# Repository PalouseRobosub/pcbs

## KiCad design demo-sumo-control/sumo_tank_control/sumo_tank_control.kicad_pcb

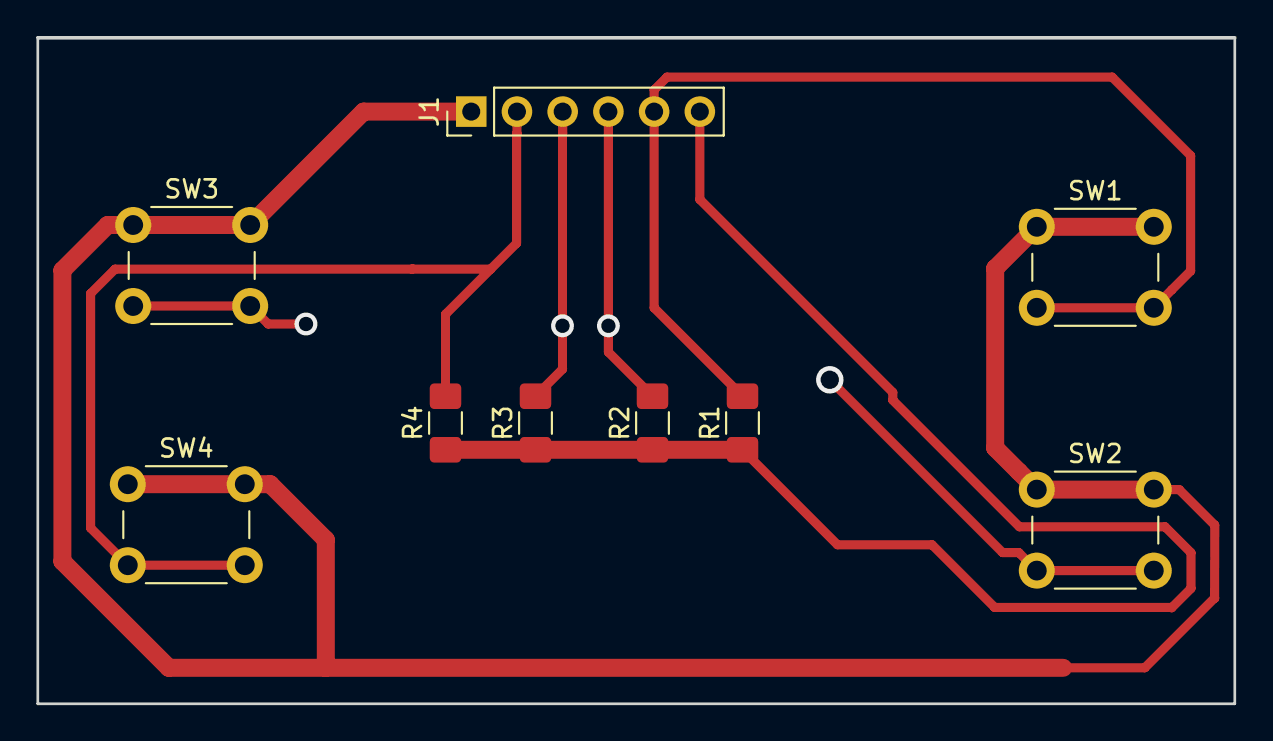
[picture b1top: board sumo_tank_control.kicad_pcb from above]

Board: 2 copper layers, 66.5 x 37.0 mm, 9 parts (0 on the bottom side), 6 nets.

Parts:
J1: Conn_01x06; PinHeader_1x06_P2.54mm_Vertical
R1, R2, R3, R4: 6k; R_1206_3216Metric_Pad1.42x1.75mm_HandSolder
SW1, SW2, SW3, SW4: SW_Push; SW_PUSH_6mm_H5mm

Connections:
+3V3: J1.6, R1.1, R2.1, R3.1, R4.1
/GPIO_0: J1.5, R1.2, SW1.2
/GPIO_1: J1.4, R2.2, SW2.2
/GPIO_2: J1.3, R3.2, SW3.2
/GPIO_3: J1.2, R4.2, SW4.2
GND: J1.1, SW1.1, SW2.1, SW3.1, SW4.1

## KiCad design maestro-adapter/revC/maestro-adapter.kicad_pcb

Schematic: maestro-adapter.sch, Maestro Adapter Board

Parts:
P1: CONN_01X07; Pin_Header_Straight_1x07; part number S7040-ND
P2, P3, P4, P5, P6, P7, P8, P9, P10, P11, P12, P13, P16: CONN_01X03; Pin_Header_Straight_1x03; part number S7036-ND
P14, P15: CONN_01X06; JST_PUD; part number 455-2485-ND
R1, R2, R3, R4, R5, R6, R7, R8, R9, R10, R11, R12, R13, R14, R15, R16: 0; R_0603_HandSoldering; part number 311-0.0GRCT-ND
U1, U2: Si866x; SOIC-16_3.9x9.9mm_Pitch1.27mm; part number 336-2115-5-ND
W1, W2, W3, W4, W5, W6, W7, W8, W9, W10, W11, W12: TEST_1P; Measurement_Point_Round-TH_Small

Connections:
+5V: P1.2, P2.2, P3.2, P4.2, P5.2, P6.2, P7.2, P8.2, P9.2, P10.2, P11.2, P12.2, P13.2, P16.1, P16.2, U1.1 (Vdd_1), U2.1 (Vdd_1)
/bec_esc_1: P14.3, U1.16 (Vdd_2), W9.1
/bec_esc_2: P15.3, U2.16 (Vdd_2), W10.1
/bec_gnd_1: P14.1, U1.9 (Gnd_2), W11.1
/bec_gnd_2: P15.1, U2.9 (Gnd_2), W12.1
/sig1: P8.1, R1.2
/sig1_in: R1.1, R9.2, U1.5 (A4)
/sig1_isolated: P14.4, U1.12 (B4), W1.1
/sig2: P7.1, R2.2
/sig2_in: R2.1, R10.2, U1.4 (A3)
/sig2_isolated: P14.2, U1.13 (B3), W2.1
/sig3: P10.1, R3.2
/sig3_in: R3.1, R11.2, U1.3 (A2)
/sig3_isolated: P14.6, U1.14 (B2), W3.1
/sig4: P11.1, R4.2
/sig4_in: R4.1, R12.2, U1.2 (A1)
/sig4_isolated: P14.5, U1.15 (B1), W4.1
/sig5: P12.1, R5.2
/sig5_in: R5.1, R13.1, U2.2 (A1)
/sig5_isolated: P15.5, U2.15 (B1), W5.1
/sig6: P13.1, R6.2
/sig6_in: R6.1, R14.1, U2.3 (A2)
/sig6_isolated: P15.2, U2.14 (B2), W6.1
/sig7: P5.1, R7.2
/sig7_in: R7.1, R15.1, U2.4 (A3)
/sig7_isolated: P15.6, U2.13 (B3), W7.1
/sig8: P6.1, R8.2
/sig8_in: R8.1, R16.1, U2.5 (A4)
/sig8_isolated: P15.4, U2.12 (B4), W8.1
/t1: P2.1, R9.1, R13.2
/t2: P3.1, R10.1, R14.2
/t3: P4.1, R11.1, R15.2
/t4: P9.1, R12.1, R16.2
GND: P1.1, P2.3, P3.3, P4.3, P5.3, P6.3, P7.3, P8.3, P9.3, P10.3, P11.3, P12.3, P13.3, P16.3, U1.8 (Gnd_1), U2.8 (Gnd_1)

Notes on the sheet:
Signal Isolators
Thruster Signals 1-4
Thruster Signals 5-8
Thruster Signals 9-12
Maestro Power Header
Thruster Case Cable Bundles
Case #2
Solder bridges can be used to short over different signals to different inputs on the isolators. This is for potential faults within the maestro.
Solder bridge connections must be shorted to mux inputs for the input signals to be transmitted.
Test Points
Power Connector
Maestro Connections
Note: tx signals are unused maestro PWM connections.
Solder Bridges
Case #1
This section intentionally left blank.

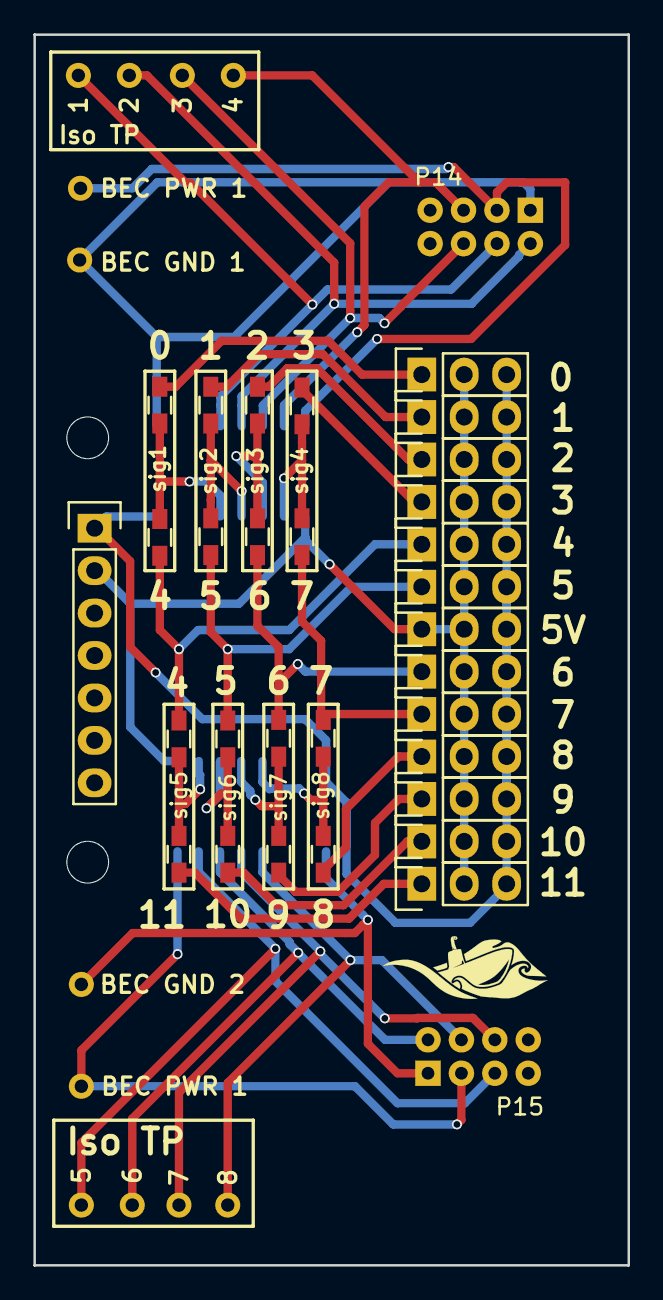
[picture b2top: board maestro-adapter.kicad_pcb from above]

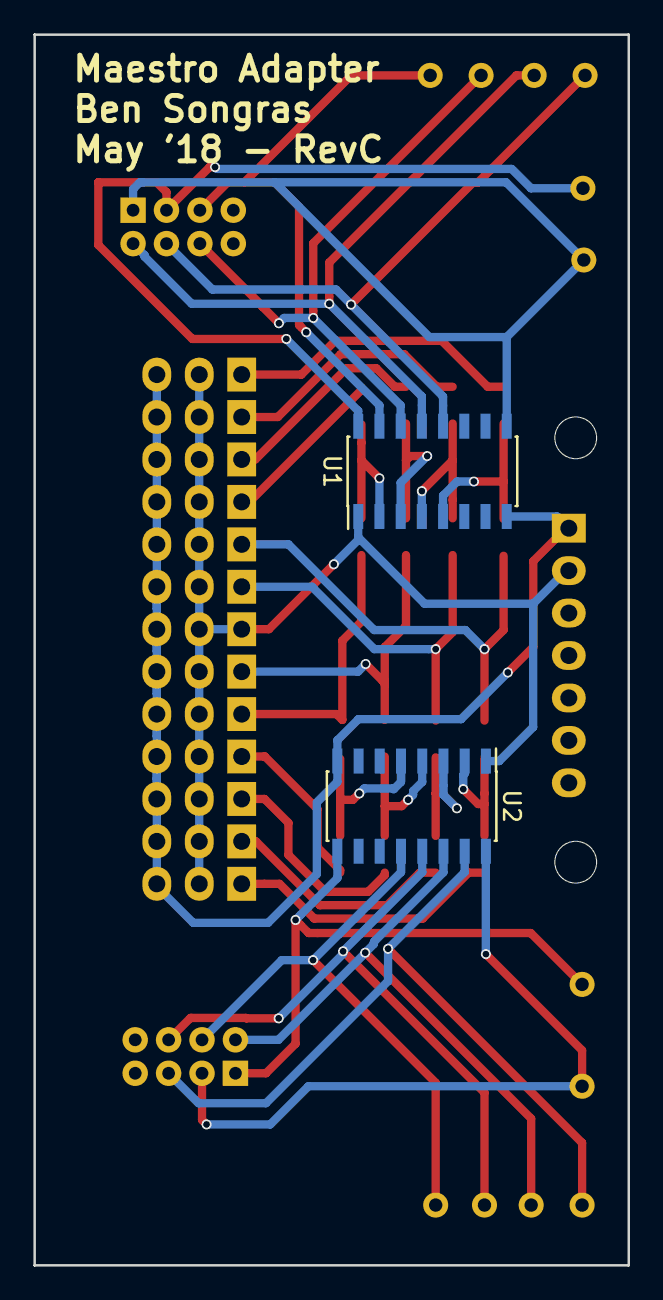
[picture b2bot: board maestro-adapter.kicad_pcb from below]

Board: 2 copper layers, 35.6 x 73.7 mm, 46 parts (2 on the bottom side), 34 nets.

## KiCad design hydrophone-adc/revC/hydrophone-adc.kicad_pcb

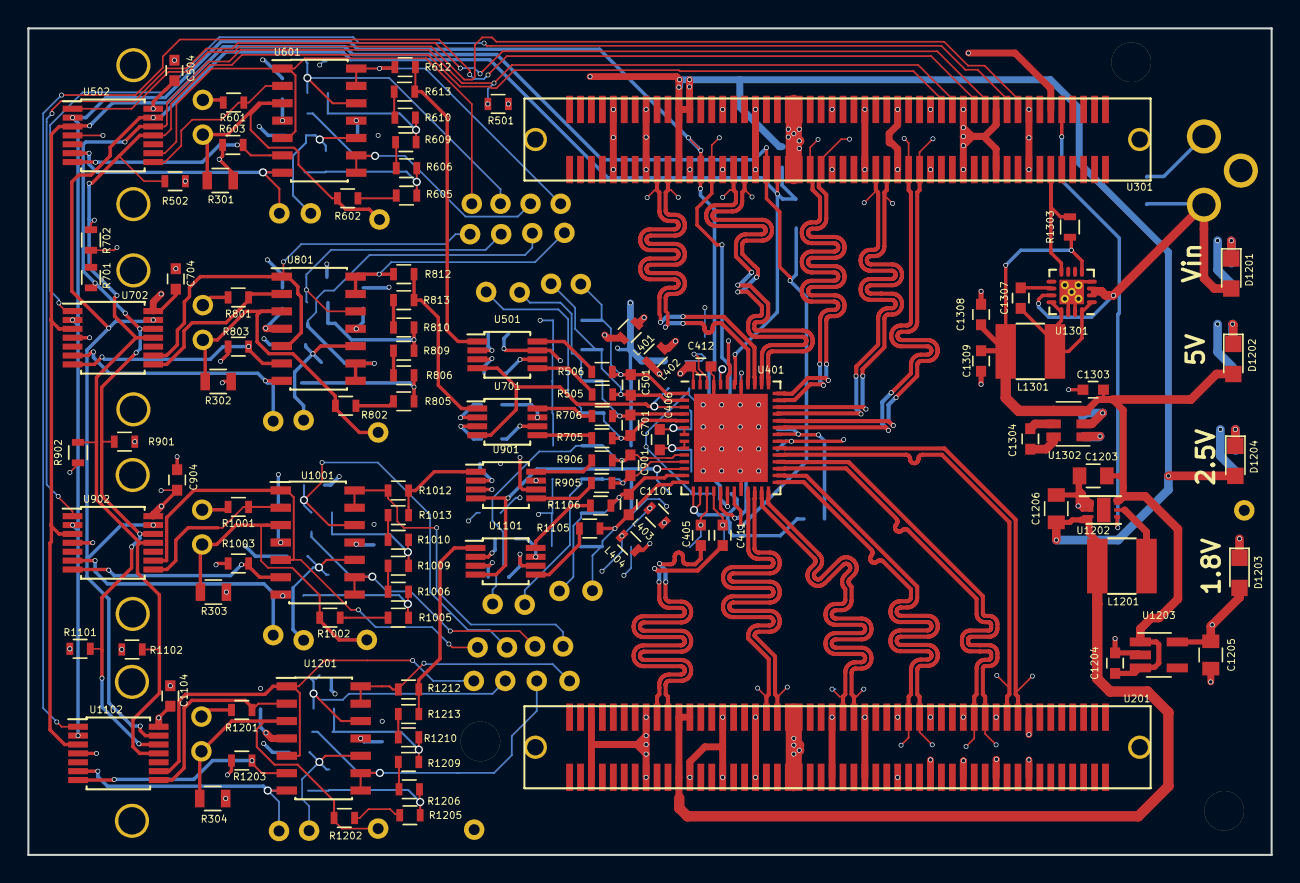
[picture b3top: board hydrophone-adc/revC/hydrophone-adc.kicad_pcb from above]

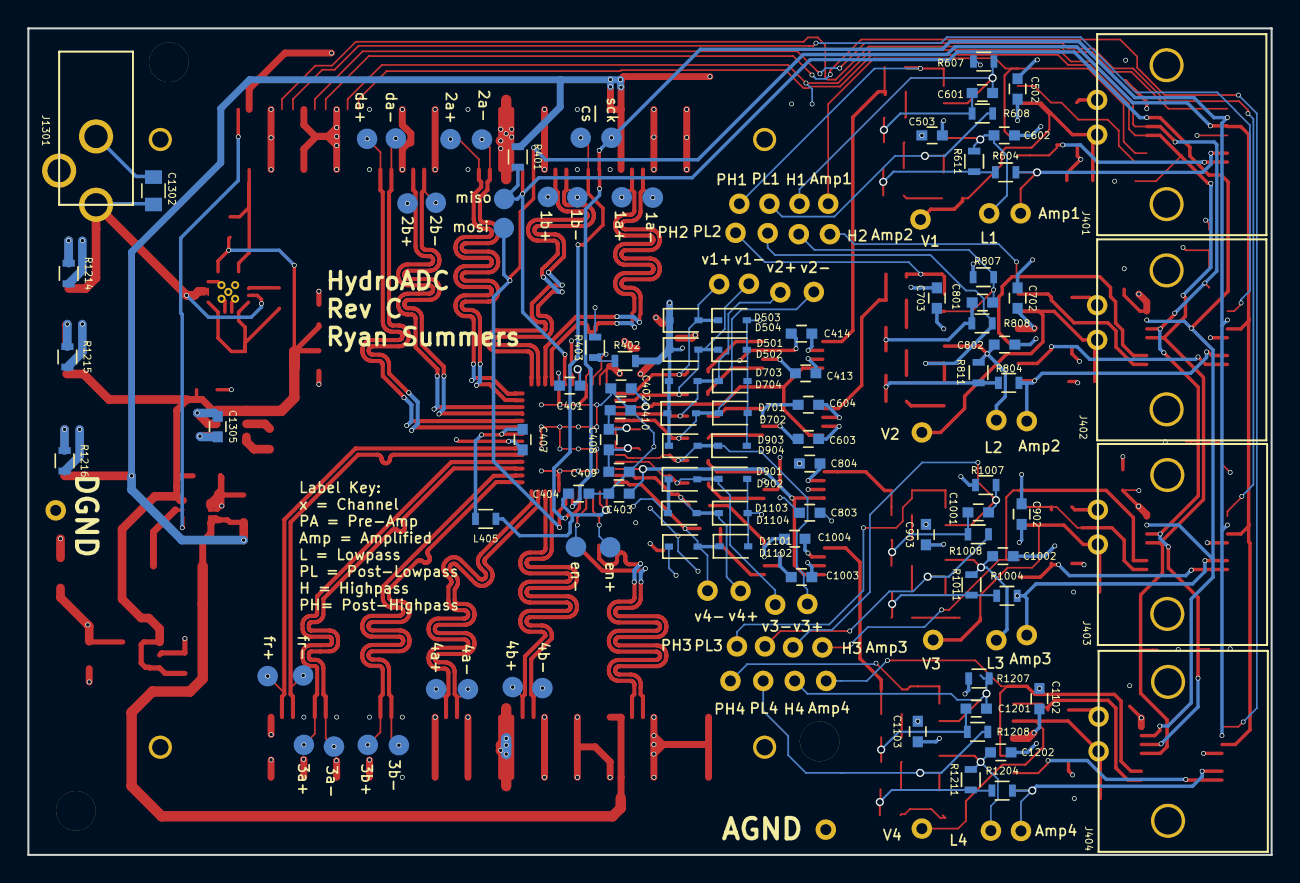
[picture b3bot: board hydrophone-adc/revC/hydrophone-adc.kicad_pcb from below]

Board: 4 copper layers, 90.9 x 60.5 mm, 249 parts (104 on the bottom side), 134 nets.

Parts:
C401, C412, C1204, C1304: 1u; C_0603
C402, C403, C404, C405, C406, C407, C409, C410, C411, C413, C414, C502, C503, C504, C603, C604, C702, C703, C704, C803, C804, C902, C903, C904, C1003, C1004, C1102, C1103, C1104: 100n; C_0603
C408, C1303, C1305: 2.2u; C_0603
C501, C701, C901, C1101: 10n; C_0603
C601, C602, C801, C802, C1001, C1002, C1201, C1202: 1n; C_0603
C1203, C1205, C1206, C1302: 10u; C_0805
C1307: 22n; C_0603
C1308, C1309: 22u; C_0603
D501, D502, D503, D504, D701, D702, D703, D704, D901, D902, D903, D904, D1101, D1102, D1103, D1104: D_Schottky; D_SOD-323
D1201: YLW; LED_0805
D1202: RED; LED_0805
D1203, D1204: GRN; LED_0805
J401, J402, J403, J404: CONN_COAXIAL; BNC-Coax-TE
J501, J502, J601, J602, J603, J604, J605, J606, J607, J701, J702, J801, J802, J803, J804, J805, J806, J807, J901, J902, J1001, J1002, J1003, J1004, J1005, J1006, J1007, J1101, J1102, J1201, J1202, J1203, J1204, J1205, J1206, J1207: TEST_1P; Measurement_Point_Round-TH_Small
J1301: BARREL_JACK; BarrelJack-CUI
L401, L402, L403, L404, L405: Ferrite_Bead; R_0603
L1201, L1301: 4.7u; Inductor-3.6mm-Pitch-4.0mm-Length-1.5mm-Width
R301, R302, R303, R304: 100k; R_0805
R401: 2k; R_0603
R402, R403, R602, R604, R605, R606, R608, R609, R610, R612, R613, R802, R804, R805, R806, R808, R809, R810, R812, R813, R1002, R1004, R1005, R1006, R1008, R1009, R1010, R1012, R1013, R1202, R1204, R1205, R1206, R1208, R1209, R1210, R1212, R1213: 0; R_0603
R501, R502, R601, R603, R607, R701, R702, R801, R803, R807, R901, R902, R1001, R1003, R1007, R1101, R1102, R1201, R1203, R1207, R1303: 10k; R_0603
R505, R506, R705, R706, R905, R906, R1105, R1106: 100; R_0603
R611, R811, R1011, R1211: 3.16k; R_0603
R1214, R1215: 1k; R_0603
R1216: 500; R_0603
TP301, TP302, TP303, TP304, TP305, TP306, TP307, TP308, TP309, TP310, TP311, TP312, TP313, TP314, TP315, TP316, TP317, TP318, TP319, TP320, TP321, TP322, TP323, TP324, TP325, TP326: TEST; Measurement_Point_Round-SMD-Pad_Small
TP327, TP328: TEST; Measurement_Point_Round-TH_Small
U201: micro-zed-jx1; fci-61083-2x50
U301: micro-zed-jx2; fci-61083-2x50
U401: LTC2171-14; QFN-52-1EP_7x8mm_Pitch0.5mm
U501, U701, U901, U1101: el5170; MSOP-8_3x3mm_Pitch0.65mm
U502, U702, U902, U1102: MCP42x1; TSSOP-14_4.4x5mm_Pitch0.65mm
U601, U801, U1001, U1201: LM324; SOIC-14_3.9x8.7mm_Pitch1.27mm
U1202: XC9261; UFDFN-6
U1203: xc6222; SOT-23-5_HandSoldering
U1301: TS30013; QFN-16-1EP_3x3mm_Pitch0.5mm_ThermalVias
U1302: LM2776; SOT-23-6

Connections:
+1V8: C407.1, C1205.1, D501.1, D503.1, D701.1, D703.1, D901.1, D903.1, D1101.1, D1103.1, D1203.2, L405.2, R402.2, U401.34, U1203.5
+2V5: C504.1, C704.1, C904.1, C1104.1, C1206.1, D1204.2, L1201.2, R401.1, R501.1, R502.1, R701.1, R702.1, R901.1, R902.1, R1101.1, R1102.1, U201.78, U201.79, U201.80, U301.78, U301.79, U301.80, U502.14, U702.14, U902.14, U1102.14, U1202.3
+5V: C413.1, C502.1, C603.1, C702.1, C803.1, C902.1, C1003.1, C1102.1, C1203.1, C1204.1, C1303.1, C1308.1, C1309.1, D1202.2, L1301.2, R1303.1, U201.57, U201.58, U201.59, U201.60, U301.12, U301.57, U301.58, U301.59, U301.60, U501.6, U601.4, U701.6, U801.4, U901.6, U1001.4, U1101.6, U1201.4, U1202.6, U1203.1, U1203.3, U1301.5, U1302.3, U1302.4
-5V: C414.1, C503.1, C604.1, C703.1, C804.1, C903.1, C1004.1, C1103.1, C1305.1, U501.7, U601.11, U701.7, U801.11, U901.7, U1001.11, U1101.7, U1201.11, U1302.1
/ADC/1v8_analog: C404.1, C412.1, L405.1, U401.15, U401.16, U401.51, U401.52
/ADC/Diff Conv1/Vin: R612.1, R613.1, U501.1
/ADC/Diff Conv1/v+: R506.1, U501.8
/ADC/Diff Conv1/v-: R505.1, U501.5
/ADC/Diff Conv2/Vin: R812.1, R813.1, U701.1
/ADC/Diff Conv2/v+: R706.1, U701.8
/ADC/Diff Conv2/v-: R705.1, U701.5
/ADC/Diff Conv3/Vin: R1012.1, R1013.1, U901.1
/ADC/Diff Conv3/v+: R906.1, U901.8
/ADC/Diff Conv3/v-: R905.1, U901.5
/ADC/Diff Conv4/Vin: R1212.1, R1213.1, U1101.1
/ADC/Diff Conv4/v+: R1106.1, U1101.8
/ADC/Diff Conv4/v-: R1105.1, U1101.5
/ADC/Filter1/P0A: R601.2, U502.8, U601.2
/ADC/Filter1/P0W: J602.1, U502.9, U601.1, U601.5
/ADC/Filter1/P1A: R603.2, U502.7, U601.6
/ADC/Filter1/P1W: J603.1, R604.2, U502.6, U601.7
/ADC/Filter1/Vin: J401.1, J601.1, R301.1, R602.1, U601.3
/ADC/Filter2/P0A: R801.2, U702.8, U801.2
/ADC/Filter2/P0W: J802.1, U702.9, U801.1, U801.5
/ADC/Filter2/P1A: R803.2, U702.7, U801.6
/ADC/Filter2/P1W: J803.1, R804.2, U702.6, U801.7
/ADC/Filter2/Vin: J402.1, J801.1, R302.1, R802.1, U801.3
/ADC/Filter3/P0A: R1001.2, U902.8, U1001.2
/ADC/Filter3/P0W: J1002.1, U902.9, U1001.1, U1001.5
/ADC/Filter3/P1A: R1003.2, U902.7, U1001.6
/ADC/Filter3/P1W: J1003.1, R1004.2, U902.6, U1001.7
/ADC/Filter3/Vin: J403.1, J1001.1, R303.1, R1002.1, U1001.3
/ADC/Filter4/P0A: R1201.2, U1102.8, U1201.2
/ADC/Filter4/P0W: J1202.1, U1102.9, U1201.1, U1201.5
/ADC/Filter4/P1A: R1203.2, U1102.7, U1201.6
/ADC/Filter4/P1W: J1203.1, R1204.2, U1102.6, U1201.7
/ADC/Filter4/Vin: J404.1, J1201.1, R304.1, R1202.1, U1201.3
/ADC/Vcm12: C402.1, U401.3, U501.4, U701.4
/ADC/Vcm34: C403.1, U401.12, U901.4, U1101.4
/ADC/enc+: C405.2, TP317.1, U401.17
/ADC/enc-: C411.2, TP318.1, U401.18
/ADC/v1+: C501.2, D503.2, D504.1, J502.1, R506.2, U401.1
/ADC/v1-: C501.1, D501.2, D502.1, J501.1, R505.2, U401.2
/ADC/v2+: C701.2, D703.2, D704.1, J702.1, R706.2, U401.4
/ADC/v2-: C701.1, D701.2, D702.1, J701.1, R705.2, U401.5
/ADC/v3+: C901.2, D903.2, D904.1, J902.1, R906.2, U401.10
/ADC/v3-: C901.1, D901.2, D902.1, J901.1, R905.2, U401.11
/ADC/v4+: C1101.2, D1103.2, D1104.1, J1102.1, R1106.2, U401.13
/ADC/v4-: C1101.1, D1101.2, D1102.1, J1101.1, R1105.2, U401.14
/MISO: R401.2, TP321.1, U301.61, U401.46, U502.13, U702.13, U902.13, U1102.13
/MOSI: TP322.1, U301.63, U401.21, U502.3, U702.3, U902.3, U1102.3
/MicroZed-JX2/LVDS1+: U301.18, U502.1
/MicroZed-JX2/LVDS1-: U301.20, U702.1
/MicroZed-JX2/LVDS3+: U301.24, U902.1
/MicroZed-JX2/LVDS3-: U301.26, U1102.1
/MicroZed-JX2/LVDS5+: R501.2, R701.2, R901.2, R1101.2, U301.30, U502.12, U702.12, U902.12, U1102.12
/MicroZed-JX2/LVDS5-: R502.2, R702.2, R902.2, R1102.2, U301.32, U502.11, U702.11, U902.11, U1102.11
/Power/Vin: C1302.1, D1201.2, J1301.1, U1301.2, U1301.3, U1301.11
/SCK: TP319.1, U301.75, U401.20, U502.2, U702.2, U902.2, U1102.2
/data_clk+: TP325.1, U301.35, U401.36
/data_clk-: TP326.1, U301.37, U401.35
/enc+: C405.1, U201.82
/enc-: C411.1, U201.84
/fr_clk+: TP323.1, U201.18, U401.32
/fr_clk-: TP324.1, U201.20, U401.31
/out1a+: TP301.1, U301.81, U401.44
/out1a-: TP309.1, U301.83, U401.43
/out1b+: TP310.1, U301.67, U401.42
/out1b-: TP302.1, U301.69, U401.41
/out2a+: TP303.1, U301.53, U401.40
/out2a-: TP311.1, U301.55, U401.39
/out2b+: TP312.1, U301.41, U401.38
/out2b-: TP304.1, U301.43, U401.37
/out3a+: TP305.1, U201.24, U401.30
/out3a-: TP313.1, U201.26, U401.29
/out3b+: TP314.1, U201.36, U401.28
/out3b-: TP306.1, U201.38, U401.27
/out4a+: TP315.1, U201.48, U401.26
/out4a-: TP307.1, U201.50, U401.25
/out4b+: TP316.1, U201.62, U401.24
/out4b-: TP308.1, U201.64, U401.23
/v_good: R1303.2, U301.11, U1301.8
/vccio_en: U301.10, U1202.4
/~CS: TP320.1, U301.73, U401.19
GND: C407.2, C1203.2, C1204.2, C1205.2, C1206.2, C1302.2, C1303.2, C1305.2, C1308.2, C1309.2, D1203.1, J1301.2, L401.1, L402.1, L403.1, L404.1, R403.1, R1214.2, R1215.2, R1216.2, TP327.1, U201.15, U201.16, U201.21, U201.22, U201.27, U201.28, U201.33, U201.34, U201.39, U201.40, U201.45, U201.46, U201.51, U201.52, U201.65, U201.66, U201.71, U201.72, U201.77, U201.85, U201.86, U201.95, U201.96, U301.15, U301.16, U301.21, U301.22, U301.27, U301.28, U301.33, U301.34, U301.39, U301.40, U301.45, U301.46, U301.51, U301.52, U301.65, U301.66, U301.71, U301.72, U301.77, U301.85, U301.86, U301.91, U301.92, U401.33, U401.47, U1202.1, U1202.2, U1203.2, U1301.4, U1301.14, U1301.15, U1301.17, U1302.2
GNDREF: C401.2, C402.2, C403.2, C404.2, C409.1, C410.2, C412.2, C413.2, C414.2, C502.2, C503.2, C504.2, C602.1, C603.2, C604.2, C702.2, C703.2, C704.2, C802.1, C803.2, C804.2, C902.2, C903.2, C904.2, C1002.1, C1003.2, C1004.2, C1102.2, C1103.2, C1104.2, C1202.1, D502.2, D504.2, D702.2, D704.2, D902.2, D904.2, D1102.2, D1104.2, J401.2, J402.2, J403.2, J404.2, L401.2, L402.2, L403.2, L404.2, R301.2, R302.2, R303.2, R304.2, R601.1, R603.1, R607.2, R801.1, R803.1, R807.2, R1001.1, R1003.1, R1007.2, R1201.1, R1203.1, R1207.2, TP328.1, U401.22, U401.45, U401.49, U401.53, U501.2, U501.3, U502.4, U701.2, U701.3, U702.4, U901.2, U901.3, U902.4, U1101.2, U1101.3, U1102.4
unnamed: C401.1, U401.48
unnamed: C406.1, C408.1, C410.1, U401.6, U401.7
unnamed: C406.2, C408.2, C409.2, U401.8, U401.9
unnamed: C601.1, J606.1, R607.1, U601.12
unnamed: C601.2, R608.1, R609.1, R610.1
unnamed: C602.2, J604.1, R611.1, U601.10
unnamed: C801.1, J806.1, R807.1, U801.12
unnamed: C801.2, R808.1, R809.1, R810.1
unnamed: C802.2, J804.1, R811.1, U801.10
unnamed: C1001.1, J1006.1, R1007.1, U1001.12
unnamed: C1001.2, R1008.1, R1009.1, R1010.1
unnamed: C1002.2, J1004.1, R1011.1, U1001.10
unnamed: C1201.1, J1206.1, R1207.1, U1201.12
unnamed: C1201.2, R1208.1, R1209.1, R1210.1
unnamed: C1202.2, J1204.1, R1211.1, U1201.10
unnamed: C1304.1, U1302.5
unnamed: C1304.2, U1302.6
unnamed: C1307.1, L1301.1, U1301.1, U1301.12, U1301.13, U1301.16
unnamed: C1307.2, U1301.10
unnamed: D1201.1, R1214.1
unnamed: D1202.1, R1215.1
unnamed: D1204.1, R1216.1
unnamed: J605.1, R608.2, U601.8, U601.9
unnamed: J607.1, R612.2, U601.13, U601.14
unnamed: J805.1, R808.2, U801.8, U801.9
unnamed: J807.1, R812.2, U801.13, U801.14
unnamed: J1005.1, R1008.2, U1001.8, U1001.9
unnamed: J1007.1, R1012.2, U1001.13, U1001.14
unnamed: J1205.1, R1208.2, U1201.8, U1201.9
unnamed: J1207.1, R1212.2, U1201.13, U1201.14
unnamed: L1201.1, U1202.5
unnamed: R402.1, R403.2, U401.50
unnamed: R602.2, R605.2
unnamed: R604.1, R605.1, R606.1, R611.2
unnamed: R606.2, R609.2
unnamed: R610.2, R613.2
unnamed: R802.2, R805.2
unnamed: R804.1, R805.1, R806.1, R811.2
unnamed: R806.2, R809.2
unnamed: R810.2, R813.2
unnamed: R1002.2, R1005.2
unnamed: R1004.1, R1005.1, R1006.1, R1011.2
unnamed: R1006.2, R1009.2
unnamed: R1010.2, R1013.2
unnamed: R1202.2, R1205.2
unnamed: R1204.1, R1205.1, R1206.1, R1211.2
unnamed: R1206.2, R1209.2
unnamed: R1210.2, R1213.2

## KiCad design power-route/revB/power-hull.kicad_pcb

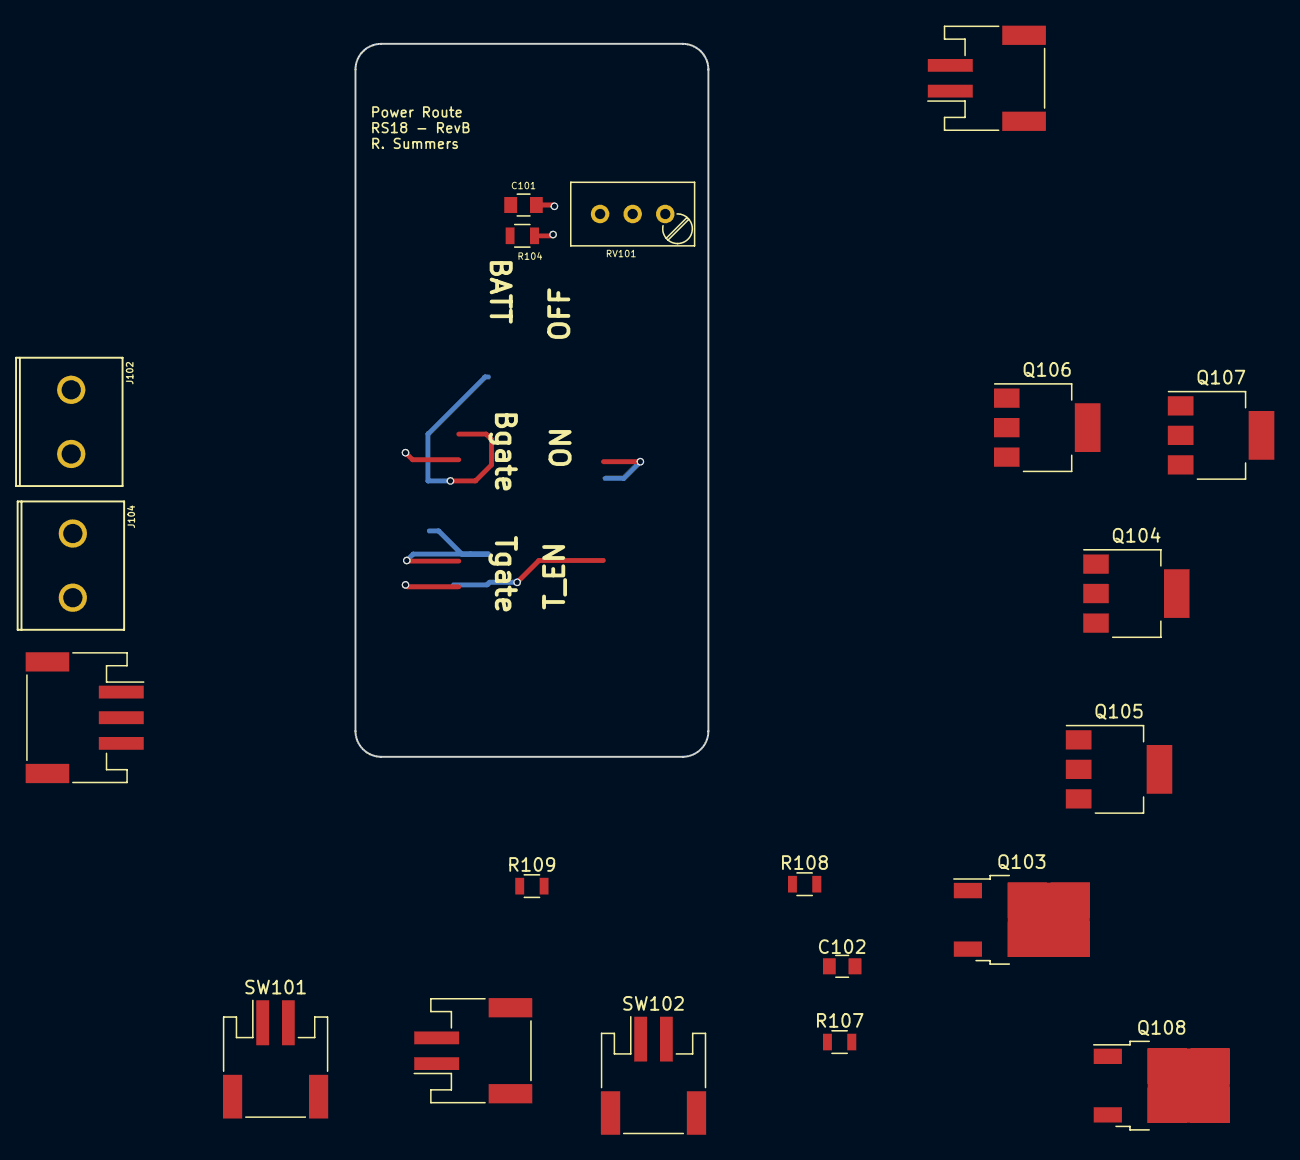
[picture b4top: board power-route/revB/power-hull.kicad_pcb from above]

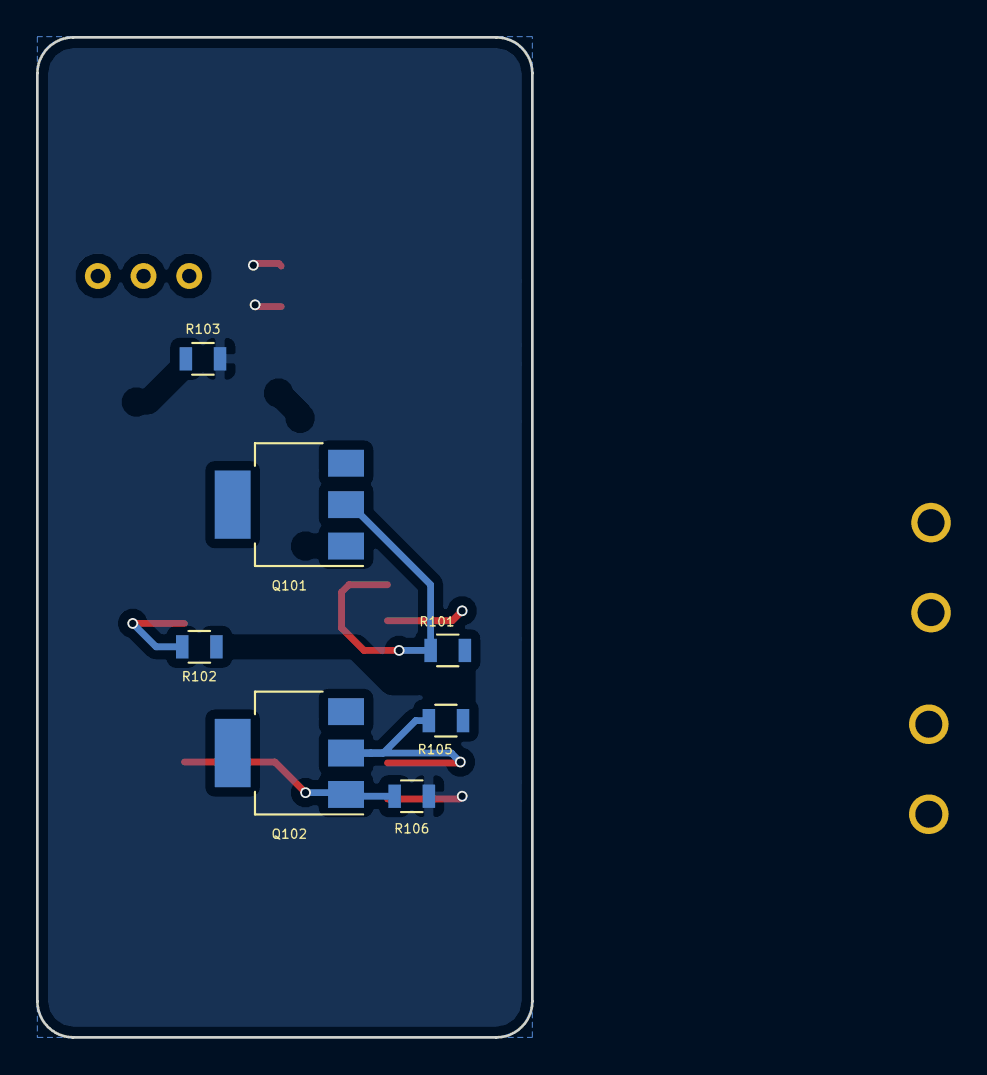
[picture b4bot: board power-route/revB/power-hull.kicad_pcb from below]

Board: 2 copper layers, 27.5 x 55.6 mm, 27 parts (7 on the bottom side), 17 nets.

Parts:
C101, C102: 1u; C_0805
J101: CONN_01X03; JST_PH_S3B-PH-SM4-TB_03x2.00mm_Angled
J102, J104: Screw_Terminal_01x02; Screw-Terminal-2-5.00mm
J103: CONN_01X02; JST_PH_S2B-PH-SM4-TB_02x2.00mm_Angled
Q101, Q102, Q104, Q105, Q106, Q107: Q_NMOS_GDS; SOT-223
Q103, Q108: Q_PMOS_GDS; TO-252-2
R101, R104, R105, R106, R107, R108, R109: 10k; R_0805
R102, R103: 1k; R_0805
RV101: POT; Potentiometer_Trimmer_Bourns_3296W
SW101: SW_ON; JST_PH_S2B-PH-SM4-TB_02x2.00mm_Angled
SW102: SW_OFF; JST_PH_S2B-PH-SM4-TB_02x2.00mm_Angled
SW103: SW_TEN; JST_PH_S2B-PH-SM4-TB_02x2.00mm_Angled

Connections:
/Bgate: J101.1, Q101.2, R101.2
/ON: C101.1, Q101.1, Q105.1, R104.1, RV101.1, SW101.2, SW102.1
/Tgate: J101.2, Q102.2, R105.2
/Vbattery: J102.2, Q108.3, R101.1, R102.1, R105.1, R109.1
/Vbulkhead: J101.3, Q103.2, RV101.2, SW103.1
/Vcharger: J104.1, Q108.2
/Vshore: Q103.3, R107.1, R108.1
/~shore_connected: J103.1, Q104.1, Q107.1, Q108.1, R109.2
GND: C101.2, C102.2, J102.1, J103.2, J104.2, Q104.3, Q106.3, Q107.3, R103.2, R104.2, R106.2
unnamed: C102.1, Q106.1, R108.2
unnamed: Q101.3, Q107.2
unnamed: Q102.1, R106.1, SW103.2
unnamed: Q102.3, Q104.2
unnamed: Q103.1, Q105.2, R107.2
unnamed: Q105.3, Q106.2
unnamed: R102.2, SW101.1
unnamed: R103.1, SW102.2

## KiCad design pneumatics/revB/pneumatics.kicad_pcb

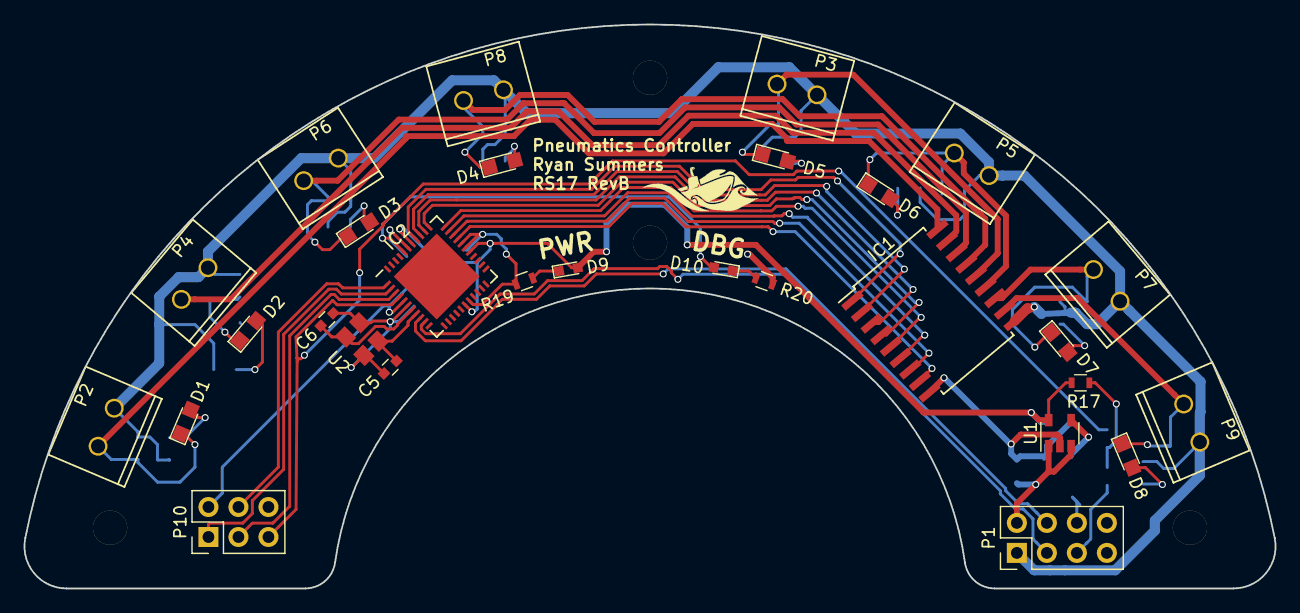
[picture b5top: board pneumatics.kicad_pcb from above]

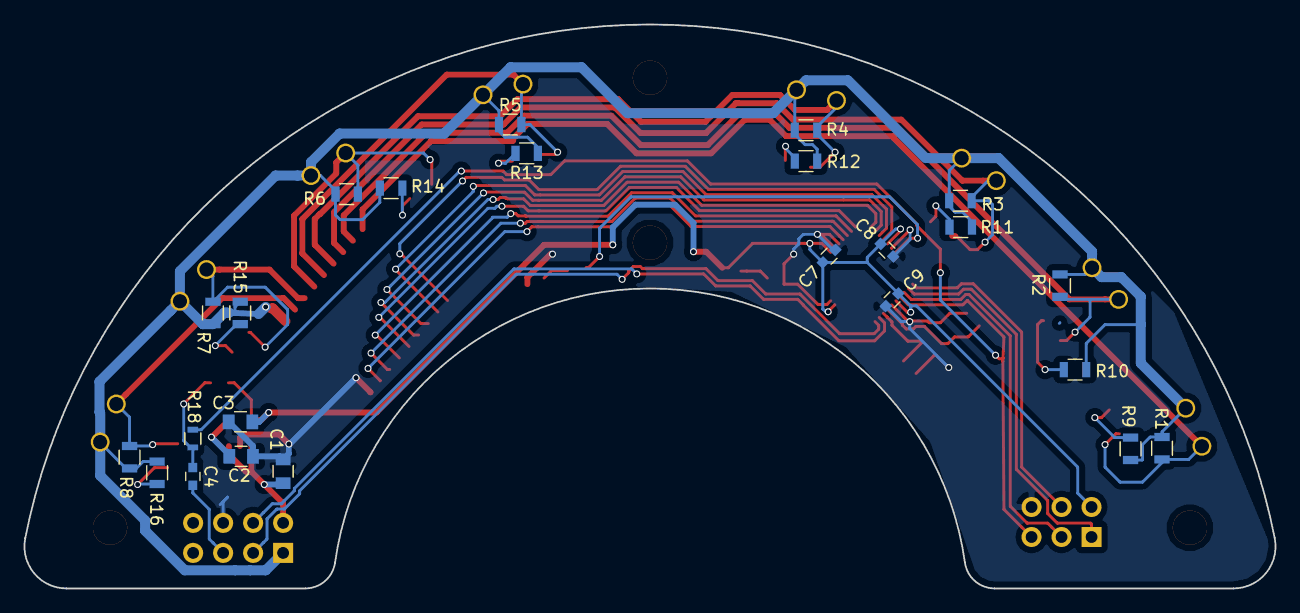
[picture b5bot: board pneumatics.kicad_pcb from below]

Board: 2 copper layers, 105.9 x 47.8 mm, 53 parts (24 on the bottom side), 42 nets.

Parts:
C1: 1u; C_0805
C2: 100p; C_0805
C3: 2.2u; C_0805
C4: 100nF; C_0603
C5, C6: 18p; C_0603
C7, C8: 100n; C_0603
C9: 4.7u; C_0603
D1, D2, D3, D4, D5, D6, D7, D8: YLW; LED_0805
D9, D10: LED; LED_0603
IC1: ULN2803A; SOIC-18W_7.5x11.6mm_Pitch1.27mm
IC2: ATMEGA1284P-M; QFN-44-1EP_7x7mm_Pitch0.5mm
P1: CONN_01X06; Pin_Header_Straight_2x04_Pitch2.54mm
P2, P3, P4, P5, P6, P7, P8, P9: CONN_01X02; Screw-Terminal-2-3.5mm
P10: CONN_02x03; Pin_Header_Straight_2x03_Pitch2.54mm
R1, R2, R3, R4, R5, R6, R7, R8, R9, R10, R11, R12, R13, R14, R15, R16: R; R_0805
R17: 10k; R_0603
R18: 1k; R_0603
R19, R20: 65; R_0603
U1: AP2210; SOT-23-5
U2: TSX-3225; DFN-4

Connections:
+3V3: C3.1, C7.1, C8.1, C9.1, D9.2, IC2.5, IC2.17, IC2.27, IC2.38, P10.2, R17.1, U1.5
+5V: C1.1, P1.2, U1.1, U1.3
+12V: IC1.10, P1.1, P2.1, P3.1, P4.1, P5.1, P6.1, P7.1, P8.1, P9.1, R1.1, R2.1, R3.1, R4.1, R5.1, R6.1, R7.1, R8.1, R9.1, R10.1, R11.1, R12.1, R13.1, R14.1, R15.1, R16.1
/Microcontroller/DBG_LED: D10.2, IC2.40
/Microcontroller/MISO: IC2.2, P10.1
/Microcontroller/MOSI: IC2.1, P10.4
/Microcontroller/SCK: IC2.3, P10.3
/Microcontroller/~RST: IC2.4, P10.5, R18.1
/PC1: IC1.1, IC2.37
/PC2: IC1.2, IC2.36
/PC3: IC1.3, IC2.35
/PC4: IC1.4, IC2.34
/PC5: IC1.5, IC2.33
/PC6: IC1.6, IC2.32
/PC7: IC1.7, IC2.31
/PC8: IC1.8, IC2.30
/PN1: D1.1, IC1.18, P2.2, R1.2
/PN2: D2.1, IC1.17, P4.2, R2.2
/PN3: D3.1, IC1.16, P6.2, R3.2
/PN4: D4.1, IC1.15, P8.2, R4.2
/PN5: D5.1, IC1.14, P3.2, R5.2
/PN6: D6.1, IC1.13, P5.2, R6.2
/PN7: D7.1, IC1.12, P7.2, R7.2
/PN8: D8.1, IC1.11, P9.2, R8.2
/dtr: C4.2, P1.5
/rx_cpu: IC2.10, P1.3
/tx_cpu: IC2.9, P1.4
GND: C1.2, C2.2, C3.2, C5.2, C6.2, C7.2, C8.2, C9.2, IC1.9, IC2.6, IC2.18, IC2.28, IC2.29, IC2.39, P1.6, P10.6, R19.2, R20.2, U1.2, U2.2, U2.4
unnamed: C2.1, U1.4
unnamed: C4.1, R17.2, R18.2
unnamed: C5.1, IC2.8, U2.3
unnamed: C6.1, IC2.7, U2.1
unnamed: D1.2, R9.2
unnamed: D2.2, R10.2
unnamed: D3.2, R11.2
unnamed: D4.2, R12.2
unnamed: D5.2, R13.2
unnamed: D6.2, R14.2
unnamed: D7.2, R15.2
unnamed: D8.2, R16.2
unnamed: D9.1, R19.1
unnamed: D10.1, R20.1
